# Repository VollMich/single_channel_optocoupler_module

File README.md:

this was designed to be a placeholder for a chinese PCB to design an enclosure in FreeCAD.

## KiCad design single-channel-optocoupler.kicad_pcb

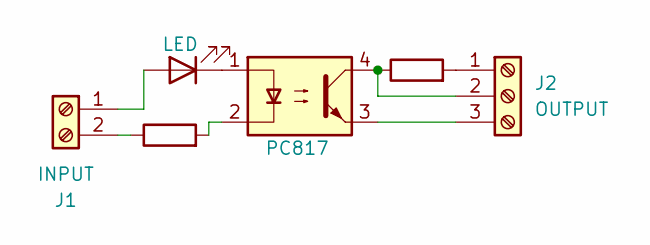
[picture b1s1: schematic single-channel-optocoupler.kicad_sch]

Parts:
D1: LED; LED_D3.0mm
J1: INPUT; TerminalBlock_Phoenix_MKDS-1,5-2_1x02_P5.00mm_Horizontal
J2: OUTPUT; TerminalBlock_Phoenix_MKDS-1,5-3_1x03_P5.00mm_Horizontal
R1, R2: R; R_Axial_DIN0204_L3.6mm_D1.6mm_P2.54mm_Vertical
U1: PC817; DIP-4_W7.62mm

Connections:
unnamed: D1.2 (A), J1.1
unnamed: D1.1 (K), U1.1
unnamed: J1.2, R1.1
unnamed: J2.1, R2.2
unnamed: J2.2, R2.1, U1.4
unnamed: J2.3, U1.3
unnamed: R1.2, U1.2

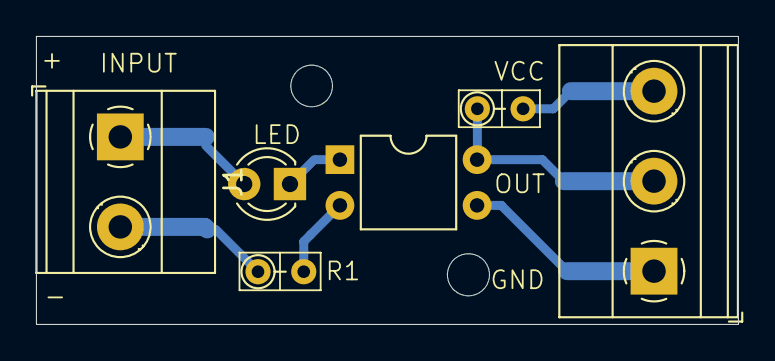
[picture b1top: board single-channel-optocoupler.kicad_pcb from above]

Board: 2 copper layers, 39.0 x 16.0 mm, 6 parts (0 on the bottom side), 7 nets.
